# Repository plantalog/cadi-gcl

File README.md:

cadi-gcl
========
Meet these two:
Cadi GCL project is an open-source plant growth controller.
Grolly - is complete plant watering and feeding solution.

Grolly system is just based on Cadi hardware

Goal: to have an irrigation system that mixes up plant feeding solutions and provides it to the root system of the plants automatically. Has communication capabilities and two main working modes - automatic and manual. Has interface for remote advanced tuning of device's behavior.

FOLDER STRUCTURE
 
android:
    - Cadi Bluetooth Monitor for Android
    
cadiweb:
	contains Cadiweb server software for Cadi Remote Control.

hardware:
    - Eagle schematics (принципиальные схемы)
    - Topor PCB layouts (дизайны плат)
    - ulp file to convert Eagle schematics to Topor (скрипт конвертиования из Eagle в Topor)
    - schematics image files (растровые изображения дизайнов плат и схем)
    - STM32 bin flashing manual (как шить STM32 контроллеры bin файлами)
    
history:
    - old versions
    
manuals:
    - Cadi manuals
    - Cadi firmware code descriptions and architecture
    
raspberry:
    - Raspberry Pi software
    
stm32f100:
    - firmwares for STM32VL-Discovery boards
    
stm32f407:
    - firmwares for STM32F4-Discovery boards
    
win32:
    - Windows Qt Bluetooth data receiver software

check http://plantalog.livejournal.com for more info

Special thanks to creators of the tools and materials I used:
Schematics made with Eagle (http://www.cadsoftusa.com/)
PCB layouts in Topor (http://eda.eremex.ru/products/topor/)
STM32 firmwares are written using CooCox IDE (coocox.org)
Putty terminal (http://www.chiark.greenend.org.uk/~sgtatham/putty/)
STM32 ANs and PMs, STM.com ST-Link utility and libraries (st.com)

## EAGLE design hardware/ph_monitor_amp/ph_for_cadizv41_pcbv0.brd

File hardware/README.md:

flashing_stm32_with_bin_file explains how to flash STM32 uC with .bin file of firmware, using STM32 ST-Link utility

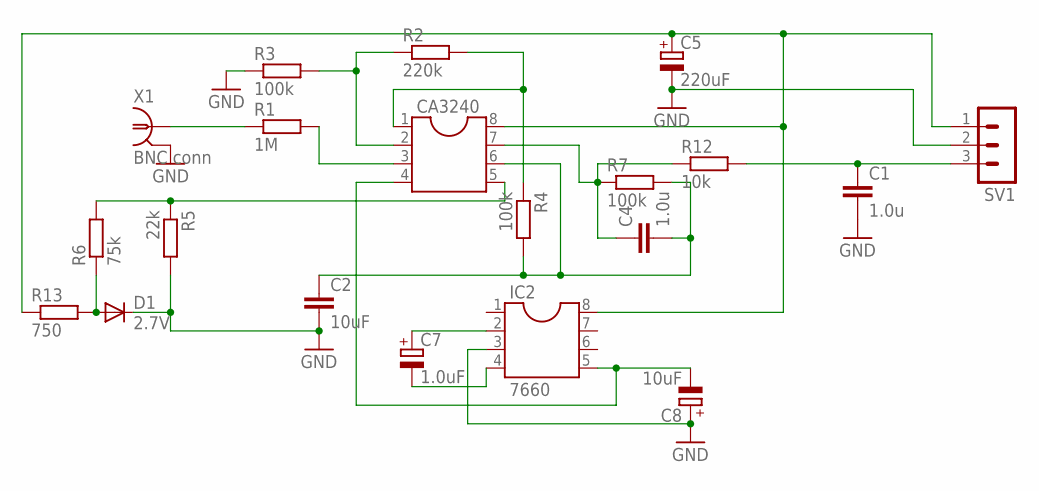
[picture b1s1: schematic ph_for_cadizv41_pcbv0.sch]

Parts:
C1, C4: 1.0u; C102-043X133
C2: 10uF; C102-043X133
C5: 220uF; E5-6
C7: 1.0uF; E5-6
C8: 10uF; E5-6
CA3240: DIL8; DIL08
D1: 2.7V; DO35-7
IC2: 7660; DIL08
R1: 1M; 0207/12
R2: 220k; 0207/12
R3, R4, R7: 100k; 0207/12
R5: 22k; 0207/12
R6: 75k; 0207/12
R12: 10k; 0207/12
R13: 750; 0207/12
SV1: MA03-1
X1: BNC conn; R141426

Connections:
GND: C1.2, C2.2, C5.-, C8.+, D1.C, IC2.3, R3.1, R5.2, SV1.2, X1.2 (GND), X1.3 (GND), X1.4 (GND), X1.5 (GND)
unnamed: CA3240.1, R2.2, R4.1
unnamed: CA3240.2, R2.1, R3.2
unnamed: CA3240.3, R1.2
unnamed: C7.+, IC2.2
unnamed: CA3240.5, R5.1, R6.2
unnamed: C7.-, IC2.4
unnamed: D1.A, R6.1, R13.2
unnamed: C4.1, CA3240.7, R7.1, R12.1
unnamed: C2.1, C4.2, CA3240.6, R4.2, R7.2
unnamed: C1.1, R12.2, SV1.3
unnamed: C8.-, CA3240.4, IC2.5
unnamed: R1.1, X1.1
unnamed: C5.+, CA3240.8, IC2.8, R13.1, SV1.1

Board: 2 copper layers, 20 parts (0 on the bottom side), 14 nets, no tracks yet.

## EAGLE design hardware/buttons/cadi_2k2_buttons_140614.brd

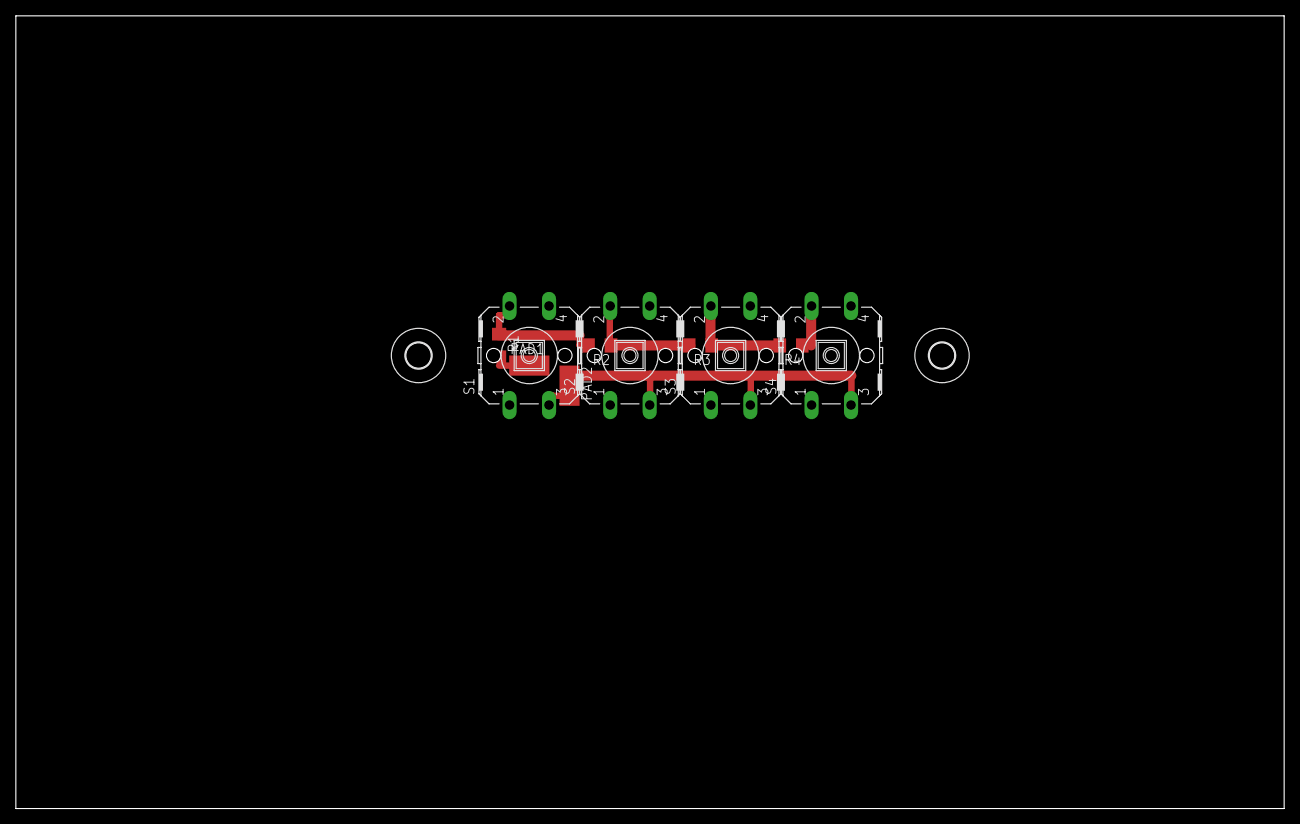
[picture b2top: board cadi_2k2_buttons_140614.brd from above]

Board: 2 copper layers, 160.0 x 100.0 mm, 12 parts (0 on the bottom side), 6 nets.

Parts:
H1, H2: MOUNT-HOLE3.2; 3,2
PAD1: VCC; SMD2,54-5,08
PAD2: TO_ADC; SMD2,54-5,08
R1, R2, R3, R4: 2k2; R1206
S1, S2, S3, S4: B3F-40XX

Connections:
unnamed: R4.1, S4.2
unnamed: R3.1, R4.2, S3.2
unnamed: R2.1, R3.2, S2.2
unnamed: R1.1, R2.2, S1.2
unnamed: PAD1.1, R1.2
unnamed: PAD2.1, S1.3, S2.3, S3.3, S4.3

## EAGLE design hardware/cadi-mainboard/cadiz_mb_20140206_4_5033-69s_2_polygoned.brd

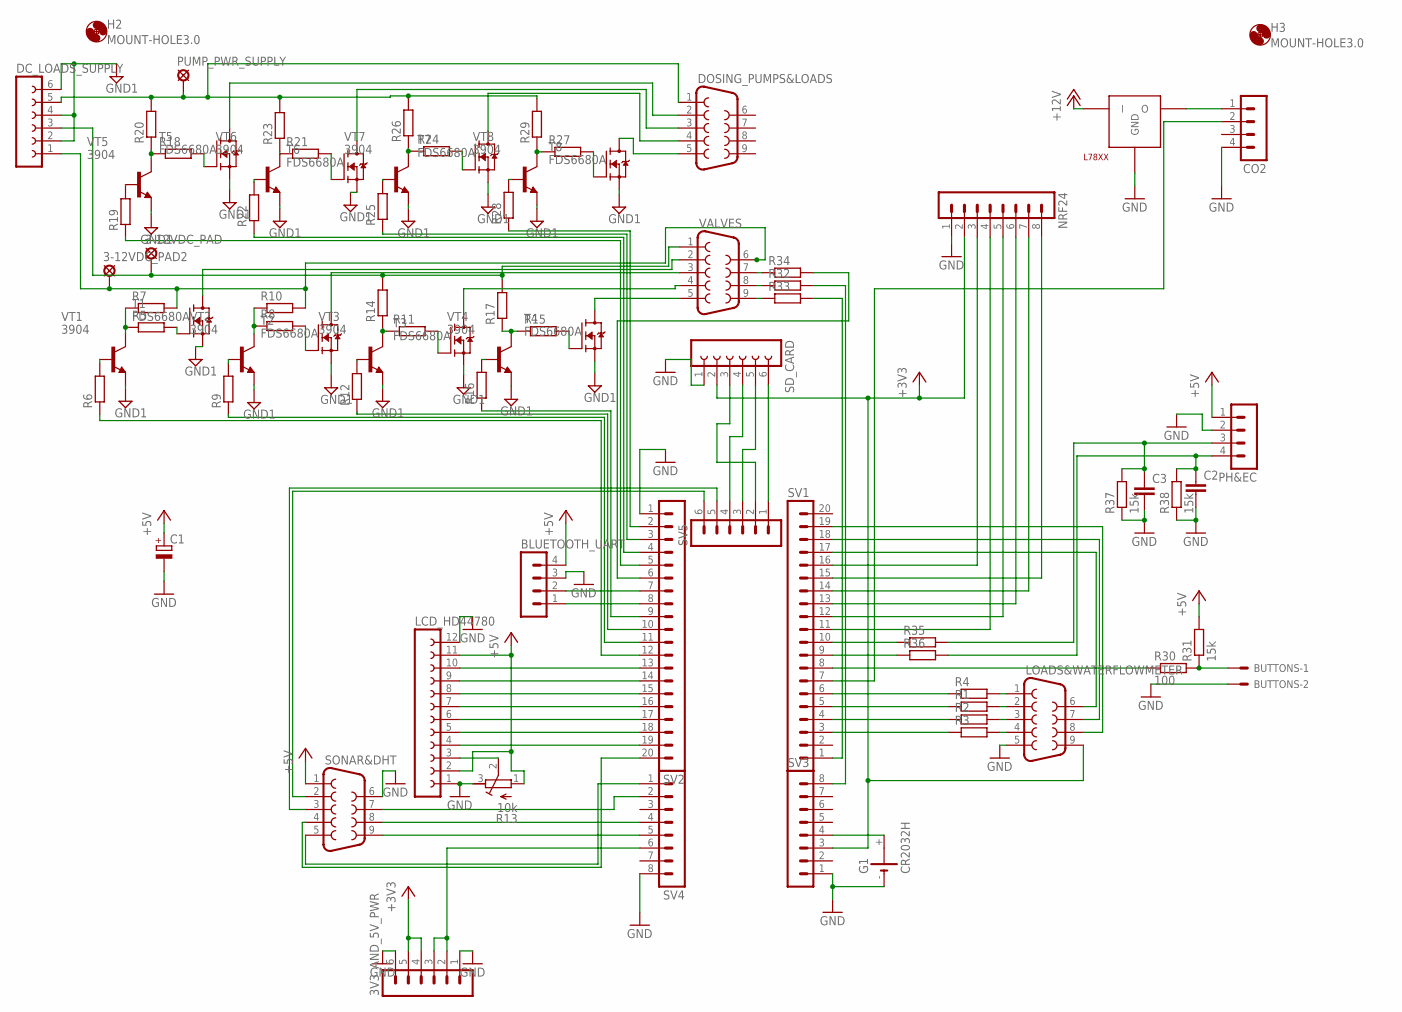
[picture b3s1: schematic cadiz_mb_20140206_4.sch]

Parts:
3-12VDC_PAD, 3-12VDC_PAD2: LSP13
3V3_AND_5V_PWR: MA06-1
BLUETOOTH_UART: MA04-1
BUTTONS: 22-23-2021
C1: CPOL-EUE5-13; E5-13
C2, C3: C-EUC1206; C1206
CO2: MA04-1
DC_LOADS_SUPPLY: FE06-1; FE06
DOSING_PUMPS&LOADS: F09HP
G1: CR2032H
H2, H3: MOUNT-HOLE3.0; 3,0
L7806: L78XX; TO220
LCD_HD44780: FE12-1; FE12
LOADS&WATERFLOWMETER: F09HP
NRF24: MA08-1
PH&EC: MA04-1
PUMP_PWR_SUPPLY: LSP13
R1, R2, R3, R4, R5, R6, R7, R8, R9, R10, R11, R12, R14, R15, R16, R17, R18, R19, R20, R21, R22, R23, R24, R25, R26, R27, R28, R29, R32, R33, R34, R35, R36: R-EU_M1206; M1206
R13: 10k; RTRIM3374
R30: 100; M1206
R31, R37, R38: 15k; M1206
SD_CARD: FE06-1; FE06
SONAR&DHT: F09HP
SV1, SV2: MA20-1
SV3, SV4: MA08-1
SV5: MA06-1
T1, T2, T3, T4, T5, T6, T7, T8: FDS6680A; SO8
VALVES: F09HP
VT1, VT2, VT3, VT4, VT5, VT6, VT7, VT8: 3904; SOT23

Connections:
+3V3: 3V3_AND_5V_PWR.4, 3V3_AND_5V_PWR.5, LOADS&WATERFLOWMETER.9, NRF24.2, SD_CARD.2, SV3.3
+5V: BLUETOOTH_UART.4, C1.+, LCD_HD44780.2, LCD_HD44780.11, PH&EC.1, R13.1 (E), R31.2, SONAR&DHT.1
+12V: L7806.IN (I)
GND: 3V3_AND_5V_PWR.1, 3V3_AND_5V_PWR.6, BLUETOOTH_UART.3, BUTTONS.2, C1.-, C2.2, C3.2, CO2.4, G1.-, L7806.GND, LCD_HD44780.1, LCD_HD44780.12, LOADS&WATERFLOWMETER.5, NRF24.1, PH&EC.2, R13.3 (A), R37.1, R38.1, SD_CARD.1, SONAR&DHT.6, SV2.1, SV3.1, SV4.8
GND1: DC_LOADS_SUPPLY.2, DC_LOADS_SUPPLY.4, DC_LOADS_SUPPLY.6, T1.SOURCE (S), T2.SOURCE (S), T3.SOURCE (S), T4.SOURCE (S), T5.SOURCE (S), T6.SOURCE (S), T7.SOURCE (S), T8.SOURCE (S), VT1.2 (E), VT2.2 (E), VT3.2 (E), VT4.2 (E), VT5.2 (E), VT6.2 (E), VT7.2 (E), VT8.2 (E)
unnamed: NRF24.6, SV1.13
unnamed: LCD_HD44780.4, SV2.19
unnamed: R16.1, SV2.9
unnamed: SONAR&DHT.2, SV5.6
unnamed: LCD_HD44780.3, R13.2 (S)
unnamed: G1.+, SV3.4
unnamed: LCD_HD44780.5, SV2.18
unnamed: LCD_HD44780.6, SV2.17
unnamed: LCD_HD44780.7, SV2.16
unnamed: LOADS&WATERFLOWMETER.3, R2.2
unnamed: LCD_HD44780.8, SV2.15
unnamed: R12.1, SV2.10
unnamed: LOADS&WATERFLOWMETER.4, R3.2
unnamed: LOADS&WATERFLOWMETER.2, R1.2
unnamed: LCD_HD44780.9, SV2.14
unnamed: LCD_HD44780.10, SV2.13
unnamed: SONAR&DHT.3, SV5.5
unnamed: R11.1, R14.1, VT3.3 (C)
unnamed: SD_CARD.6, SV5.1
unnamed: SONAR&DHT.7, SV4.2
unnamed: SD_CARD.5, SV5.3
unnamed: SD_CARD.4, SV5.4
unnamed: SONAR&DHT.8, SV4.4
unnamed: SD_CARD.3, SV5.2
unnamed: R1.1, SV1.5
unnamed: R2.1, SV1.4
unnamed: R3.1, SV1.3
unnamed: R4.1, SV1.6
unnamed: SONAR&DHT.9, SV4.5
unnamed: LOADS&WATERFLOWMETER.1, R4.2
unnamed: R8.2, T2.GATE (G)
unnamed: R5.2, T1.GATE (G)
unnamed: R6.2, VT1.1 (B)
unnamed: R9.2, VT2.1 (B)
unnamed: 3V3_AND_5V_PWR.2, 3V3_AND_5V_PWR.3, SV4.6
unnamed: R11.2, T3.GATE (G)
unnamed: R12.2, VT3.1 (B)
unnamed: R15.2, T4.GATE (G)
unnamed: R16.2, VT4.1 (B)
unnamed: R18.2, T5.GATE (G)
unnamed: R19.2, VT5.1 (B)
unnamed: R21.2, T6.GATE (G)
unnamed: R22.2, VT6.1 (B)
unnamed: R24.2, T7.GATE (G)
unnamed: R25.2, VT7.1 (B)
unnamed: R27.2, T8.GATE (G)
unnamed: R28.2, VT8.1 (B)
unnamed: 3-12VDC_PAD.MP, DC_LOADS_SUPPLY.3, R14.2, R17.2, VALVES.1
unnamed: 3-12VDC_PAD2.MP, DC_LOADS_SUPPLY.1, R7.2, R10.2, VALVES.6
unnamed: R9.1, SV2.11
unnamed: R6.1, SV2.12
unnamed: DC_LOADS_SUPPLY.5, DOSING_PUMPS&LOADS.1, PUMP_PWR_SUPPLY.MP, R20.2, R23.2, R26.2, R29.2
unnamed: BLUETOOTH_UART.1, SV2.8
unnamed: BLUETOOTH_UART.2, SV2.7
unnamed: R28.1, SV2.2
unnamed: R25.1, SV2.3
unnamed: R22.1, SV2.4
unnamed: R19.1, SV2.5
unnamed: DOSING_PUMPS&LOADS.5, T8.DRAIN (D)
unnamed: DOSING_PUMPS&LOADS.4, T7.DRAIN (D)
unnamed: DOSING_PUMPS&LOADS.3, T6.DRAIN (D)
unnamed: DOSING_PUMPS&LOADS.2, T5.DRAIN (D)
unnamed: BUTTONS.1, R30.2, R31.1
unnamed: NRF24.7, SV1.14
unnamed: NRF24.5, SV1.12
unnamed: R30.1, SV1.8
unnamed: T4.DRAIN (D), VALVES.5
unnamed: T3.DRAIN (D), VALVES.4
unnamed: T2.DRAIN (D), VALVES.3
unnamed: T1.DRAIN (D), VALVES.2
unnamed: R32.1, VALVES.8
unnamed: R33.1, VALVES.9
unnamed: R34.1, VALVES.7
unnamed: LOADS&WATERFLOWMETER.7, SV1.18
unnamed: LOADS&WATERFLOWMETER.8, SV1.19
unnamed: LOADS&WATERFLOWMETER.6, SV1.17
unnamed: SONAR&DHT.5, SV4.1
unnamed: SONAR&DHT.4, SV2.20
unnamed: NRF24.4, SV1.11
unnamed: NRF24.8, SV1.15
unnamed: NRF24.3, SV1.16
unnamed: R33.2, SV1.1
unnamed: R32.2, SV3.8
unnamed: R34.2, SV2.6
unnamed: C2.1, PH&EC.4, R36.2, R38.2
unnamed: C3.1, PH&EC.3, R35.2, R37.2
unnamed: R35.1, SV1.10
unnamed: R36.1, SV1.9
unnamed: CO2.1, L7806.OUT (O)
unnamed: CO2.2, SV1.7
VT1: R5.1, R7.1, VT1.3 (C)
VT2: R8.1, R10.1, VT2.3 (C)
VT4: R15.1, R17.1, VT4.3 (C)
VT5: R18.1, R20.1, VT5.3 (C)
VT6: R21.1, R23.1, VT6.3 (C)
VT7: R24.1, R26.1, VT7.3 (C)
VT8: R27.1, R29.1, VT8.3 (C)

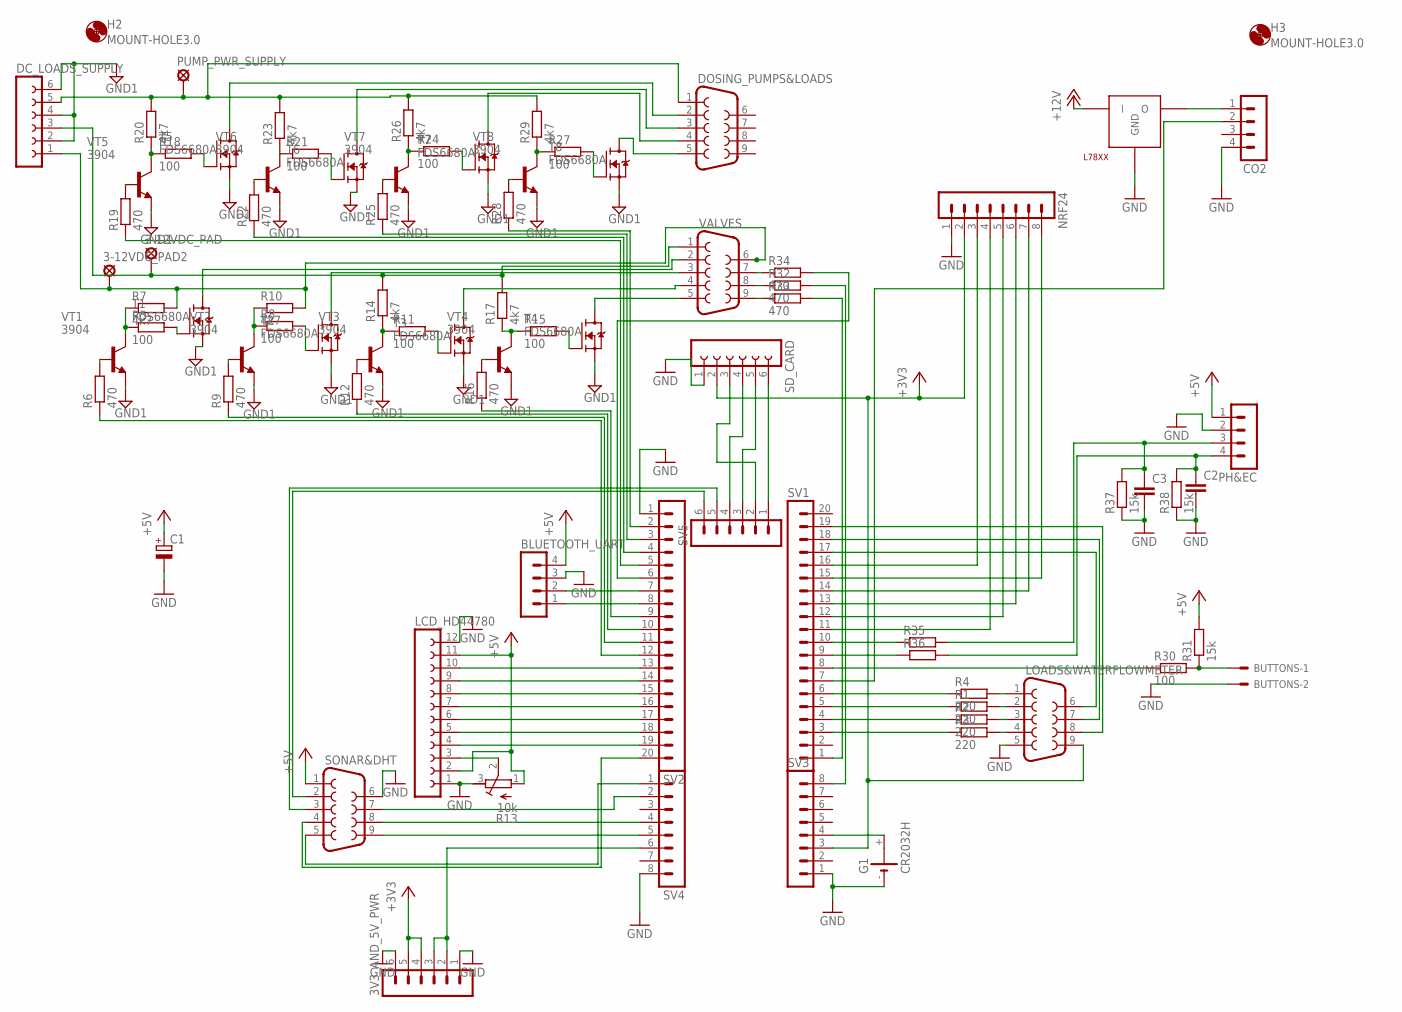
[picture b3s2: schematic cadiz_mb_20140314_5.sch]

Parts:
3-12VDC_PAD, 3-12VDC_PAD2: LSP13
3V3_AND_5V_PWR: MA06-1
BLUETOOTH_UART: MA04-1
BUTTONS: 22-23-2021
C1: CPOL-EUE5-13; E5-13
C2, C3: C-EUC1206; C1206
CO2: MA04-1
DC_LOADS_SUPPLY: FE06-1; FE06
DOSING_PUMPS&LOADS: F09HP
G1: CR2032H
H2, H3: MOUNT-HOLE3.0; 3,0
L7806: L78XX; TO220
LCD_HD44780: FE12-1; FE12
LOADS&WATERFLOWMETER: F09HP
NRF24: MA08-1
PH&EC: MA04-1
PUMP_PWR_SUPPLY: LSP13
R1, R2, R3, R4: 220; M1206
R5, R8, R11, R15, R18, R21, R24, R27, R30: 100; M1206
R6, R9, R12, R16, R19, R22, R25, R28, R32, R33, R34: 470; M1206
R7, R10, R14, R17, R20, R23, R26, R29: 4k7; M1206
R13: 10k; RTRIM3374
R31, R37, R38: 15k; M1206
R35, R36: R-EU_M1206; M1206
SD_CARD: FE06-1; FE06
SONAR&DHT: F09HP
SV1, SV2: MA20-1
SV3, SV4: MA08-1
SV5: MA06-1
T1, T2, T3, T4, T5, T6, T7, T8: FDS6680A; SO8
VALVES: F09HP
VT1, VT2, VT3, VT4, VT5, VT6, VT7, VT8: 3904; SOT23

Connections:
+3V3: 3V3_AND_5V_PWR.4, 3V3_AND_5V_PWR.5, LOADS&WATERFLOWMETER.9, NRF24.2, SD_CARD.2, SV3.3
+5V: BLUETOOTH_UART.4, C1.+, LCD_HD44780.2, LCD_HD44780.11, PH&EC.1, R13.1 (E), R31.2, SONAR&DHT.1
+12V: L7806.IN (I)
GND: 3V3_AND_5V_PWR.1, 3V3_AND_5V_PWR.6, BLUETOOTH_UART.3, BUTTONS.2, C1.-, C2.2, C3.2, CO2.4, G1.-, L7806.GND, LCD_HD44780.1, LCD_HD44780.12, LOADS&WATERFLOWMETER.5, NRF24.1, PH&EC.2, R13.3 (A), R37.1, R38.1, SD_CARD.1, SONAR&DHT.6, SV2.1, SV3.1, SV4.8
GND1: DC_LOADS_SUPPLY.2, DC_LOADS_SUPPLY.4, DC_LOADS_SUPPLY.6, T1.SOURCE (S), T2.SOURCE (S), T3.SOURCE (S), T4.SOURCE (S), T5.SOURCE (S), T6.SOURCE (S), T7.SOURCE (S), T8.SOURCE (S), VT1.2 (E), VT2.2 (E), VT3.2 (E), VT4.2 (E), VT5.2 (E), VT6.2 (E), VT7.2 (E), VT8.2 (E)
unnamed: NRF24.6, SV1.13
unnamed: LCD_HD44780.4, SV2.19
unnamed: R16.1, SV2.9
unnamed: SONAR&DHT.2, SV5.6
unnamed: LCD_HD44780.3, R13.2 (S)
unnamed: G1.+, SV3.4
unnamed: LCD_HD44780.5, SV2.18
unnamed: LCD_HD44780.6, SV2.17
unnamed: LCD_HD44780.7, SV2.16
unnamed: LOADS&WATERFLOWMETER.3, R2.2
unnamed: LCD_HD44780.8, SV2.15
unnamed: R12.1, SV2.10
unnamed: LOADS&WATERFLOWMETER.4, R3.2
unnamed: LOADS&WATERFLOWMETER.2, R1.2
unnamed: LCD_HD44780.9, SV2.14
unnamed: LCD_HD44780.10, SV2.13
unnamed: SONAR&DHT.3, SV5.5
unnamed: R11.1, R14.1, VT3.3 (C)
unnamed: SD_CARD.6, SV5.1
unnamed: SONAR&DHT.7, SV4.2
unnamed: SD_CARD.5, SV5.3
unnamed: SD_CARD.4, SV5.4
unnamed: SONAR&DHT.8, SV4.4
unnamed: SD_CARD.3, SV5.2
unnamed: R1.1, SV1.5
unnamed: R2.1, SV1.4
unnamed: R3.1, SV1.3
unnamed: R4.1, SV1.6
unnamed: SONAR&DHT.9, SV4.5
unnamed: LOADS&WATERFLOWMETER.1, R4.2
unnamed: R8.2, T2.GATE (G)
unnamed: R5.2, T1.GATE (G)
unnamed: R6.2, VT1.1 (B)
unnamed: R9.2, VT2.1 (B)
unnamed: 3V3_AND_5V_PWR.2, 3V3_AND_5V_PWR.3, SV4.6
unnamed: R11.2, T3.GATE (G)
unnamed: R12.2, VT3.1 (B)
unnamed: R15.2, T4.GATE (G)
unnamed: R16.2, VT4.1 (B)
unnamed: R18.2, T5.GATE (G)
unnamed: R19.2, VT5.1 (B)
unnamed: R21.2, T6.GATE (G)
unnamed: R22.2, VT6.1 (B)
unnamed: R24.2, T7.GATE (G)
unnamed: R25.2, VT7.1 (B)
unnamed: R27.2, T8.GATE (G)
unnamed: R28.2, VT8.1 (B)
unnamed: 3-12VDC_PAD.MP, DC_LOADS_SUPPLY.3, R14.2, R17.2, VALVES.1
unnamed: 3-12VDC_PAD2.MP, DC_LOADS_SUPPLY.1, R7.2, R10.2, VALVES.6
unnamed: R9.1, SV2.11
unnamed: R6.1, SV2.12
unnamed: DC_LOADS_SUPPLY.5, DOSING_PUMPS&LOADS.1, PUMP_PWR_SUPPLY.MP, R20.2, R23.2, R26.2, R29.2
unnamed: BLUETOOTH_UART.1, SV2.8
unnamed: BLUETOOTH_UART.2, SV2.7
unnamed: R28.1, SV2.2
unnamed: R25.1, SV2.3
unnamed: R22.1, SV2.4
unnamed: R19.1, SV2.5
unnamed: DOSING_PUMPS&LOADS.5, T8.DRAIN (D)
unnamed: DOSING_PUMPS&LOADS.4, T7.DRAIN (D)
unnamed: DOSING_PUMPS&LOADS.3, T6.DRAIN (D)
unnamed: DOSING_PUMPS&LOADS.2, T5.DRAIN (D)
unnamed: BUTTONS.1, R30.2, R31.1
unnamed: NRF24.7, SV1.14
unnamed: NRF24.5, SV1.12
unnamed: R30.1, SV1.8
unnamed: T4.DRAIN (D), VALVES.5
unnamed: T3.DRAIN (D), VALVES.4
unnamed: T2.DRAIN (D), VALVES.3
unnamed: T1.DRAIN (D), VALVES.2
unnamed: R32.1, VALVES.8
unnamed: R33.1, VALVES.9
unnamed: R34.1, VALVES.7
unnamed: LOADS&WATERFLOWMETER.7, SV1.18
unnamed: LOADS&WATERFLOWMETER.8, SV1.19
unnamed: LOADS&WATERFLOWMETER.6, SV1.17
unnamed: SONAR&DHT.5, SV4.1
unnamed: SONAR&DHT.4, SV2.20
unnamed: NRF24.4, SV1.11
unnamed: NRF24.8, SV1.15
unnamed: NRF24.3, SV1.16
unnamed: R33.2, SV1.1
unnamed: R32.2, SV3.8
unnamed: R34.2, SV2.6
unnamed: C2.1, PH&EC.4, R36.2, R38.2
unnamed: C3.1, PH&EC.3, R35.2, R37.2
unnamed: R35.1, SV1.10
unnamed: R36.1, SV1.9
unnamed: CO2.1, L7806.OUT (O)
unnamed: CO2.2, SV1.7
VT1: R5.1, R7.1, VT1.3 (C)
VT2: R8.1, R10.1, VT2.3 (C)
VT4: R15.1, R17.1, VT4.3 (C)
VT5: R18.1, R20.1, VT5.3 (C)
VT6: R21.1, R23.1, VT6.3 (C)
VT7: R24.1, R26.1, VT7.3 (C)
VT8: R27.1, R29.1, VT8.3 (C)

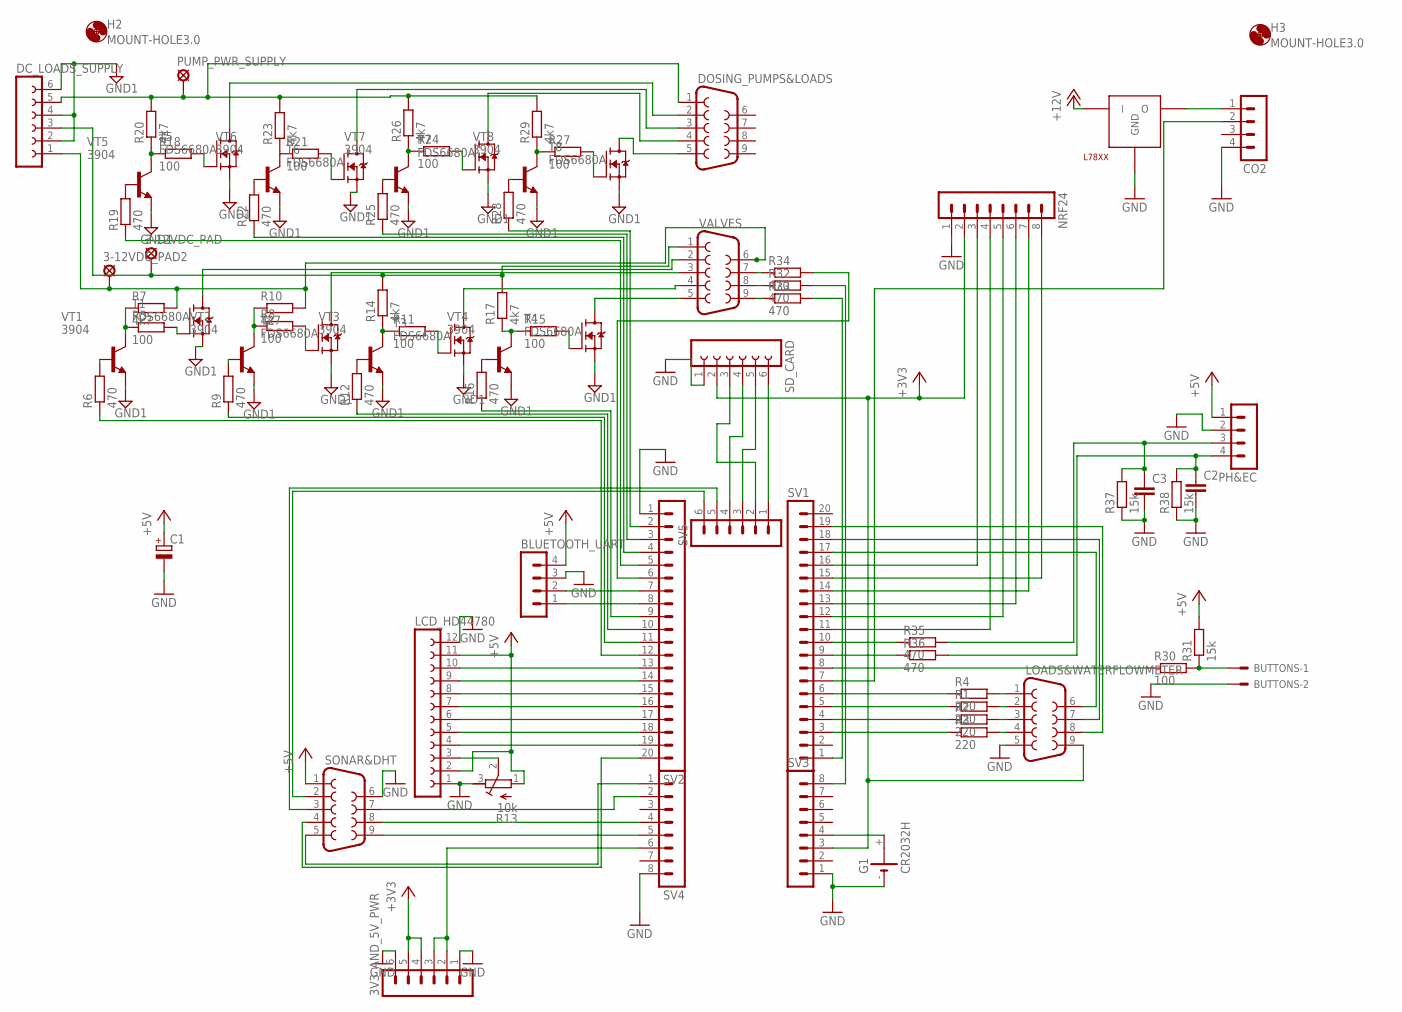
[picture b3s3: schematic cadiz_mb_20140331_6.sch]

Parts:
3-12VDC_PAD, 3-12VDC_PAD2: LSP13
3V3_AND_5V_PWR: MA06-1
BLUETOOTH_UART: MA04-1
BUTTONS: 22-23-2021
C1: CPOL-EUE5-13; E5-13
C2, C3: C-EUC1206; C1206
CO2: MA04-1
DC_LOADS_SUPPLY: FE06-1; FE06
DOSING_PUMPS&LOADS: F09HP
G1: CR2032H
H2, H3: MOUNT-HOLE3.0; 3,0
L7806: L78XX; TO220
LCD_HD44780: FE12-1; FE12
LOADS&WATERFLOWMETER: F09HP
NRF24: MA08-1
PH&EC: MA04-1
PUMP_PWR_SUPPLY: LSP13
R1, R2, R3, R4: 220; M1206
R5, R8, R11, R15, R18, R21, R24, R27, R30: 100; M1206
R6, R9, R12, R16, R19, R22, R25, R28, R32, R33, R34, R35, R36: 470; M1206
R7, R10, R14, R17, R20, R23, R26, R29: 4k7; M1206
R13: 10k; RTRIM3374
R31, R37, R38: 15k; M1206
SD_CARD: FE06-1; FE06
SONAR&DHT: F09HP
SV1, SV2: MA20-1
SV3, SV4: MA08-1
SV5: MA06-1
T1, T2, T3, T4, T5, T6, T7, T8: FDS6680A; SO8
VALVES: F09HP
VT1, VT2, VT3, VT4, VT5, VT6, VT7, VT8: 3904; SOT23

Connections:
+3V3: 3V3_AND_5V_PWR.4, 3V3_AND_5V_PWR.5, LOADS&WATERFLOWMETER.9, NRF24.2, SD_CARD.2, SV3.3
+5V: BLUETOOTH_UART.4, C1.+, LCD_HD44780.2, LCD_HD44780.11, PH&EC.1, R13.1 (E), R31.2, SONAR&DHT.1
+12V: L7806.IN (I)
GND: 3V3_AND_5V_PWR.1, 3V3_AND_5V_PWR.6, BLUETOOTH_UART.3, BUTTONS.2, C1.-, C2.2, C3.2, CO2.4, G1.-, L7806.GND, LCD_HD44780.1, LCD_HD44780.12, LOADS&WATERFLOWMETER.5, NRF24.1, PH&EC.2, R13.3 (A), R37.1, R38.1, SD_CARD.1, SONAR&DHT.6, SV2.1, SV3.1, SV4.8
GND1: DC_LOADS_SUPPLY.2, DC_LOADS_SUPPLY.4, DC_LOADS_SUPPLY.6, T1.SOURCE (S), T2.SOURCE (S), T3.SOURCE (S), T4.SOURCE (S), T5.SOURCE (S), T6.SOURCE (S), T7.SOURCE (S), T8.SOURCE (S), VT1.2 (E), VT2.2 (E), VT3.2 (E), VT4.2 (E), VT5.2 (E), VT6.2 (E), VT7.2 (E), VT8.2 (E)
unnamed: NRF24.6, SV1.13
unnamed: LCD_HD44780.4, SV2.19
unnamed: R16.1, SV2.9
unnamed: SONAR&DHT.2, SV5.6
unnamed: LCD_HD44780.3, R13.2 (S)
unnamed: G1.+, SV3.4
unnamed: LCD_HD44780.5, SV2.18
unnamed: LCD_HD44780.6, SV2.17
unnamed: LCD_HD44780.7, SV2.16
unnamed: LOADS&WATERFLOWMETER.3, R2.2
unnamed: LCD_HD44780.8, SV2.15
unnamed: R12.1, SV2.10
unnamed: LOADS&WATERFLOWMETER.4, R3.2
unnamed: LOADS&WATERFLOWMETER.2, R1.2
unnamed: LCD_HD44780.9, SV2.14
unnamed: LCD_HD44780.10, SV2.13
unnamed: SONAR&DHT.3, SV5.5
unnamed: R11.1, R14.1, VT3.3 (C)
unnamed: SD_CARD.6, SV5.1
unnamed: SONAR&DHT.7, SV4.2
unnamed: SD_CARD.5, SV5.3
unnamed: SD_CARD.4, SV5.4
unnamed: SONAR&DHT.8, SV4.4
unnamed: SD_CARD.3, SV5.2
unnamed: R1.1, SV1.5
unnamed: R2.1, SV1.4
unnamed: R3.1, SV1.3
unnamed: R4.1, SV1.6
unnamed: SONAR&DHT.9, SV4.5
unnamed: LOADS&WATERFLOWMETER.1, R4.2
unnamed: R8.2, T2.GATE (G)
unnamed: R5.2, T1.GATE (G)
unnamed: R6.2, VT1.1 (B)
unnamed: R9.2, VT2.1 (B)
unnamed: 3V3_AND_5V_PWR.2, 3V3_AND_5V_PWR.3, SV4.6
unnamed: R11.2, T3.GATE (G)
unnamed: R12.2, VT3.1 (B)
unnamed: R15.2, T4.GATE (G)
unnamed: R16.2, VT4.1 (B)
unnamed: R18.2, T5.GATE (G)
unnamed: R19.2, VT5.1 (B)
unnamed: R21.2, T6.GATE (G)
unnamed: R22.2, VT6.1 (B)
unnamed: R24.2, T7.GATE (G)
unnamed: R25.2, VT7.1 (B)
unnamed: R27.2, T8.GATE (G)
unnamed: R28.2, VT8.1 (B)
unnamed: 3-12VDC_PAD.MP, DC_LOADS_SUPPLY.3, R14.2, R17.2, VALVES.1
unnamed: 3-12VDC_PAD2.MP, DC_LOADS_SUPPLY.1, R7.2, R10.2, VALVES.6
unnamed: R9.1, SV2.11
unnamed: R6.1, SV2.12
unnamed: DC_LOADS_SUPPLY.5, DOSING_PUMPS&LOADS.1, PUMP_PWR_SUPPLY.MP, R20.2, R23.2, R26.2, R29.2
unnamed: BLUETOOTH_UART.1, SV2.8
unnamed: BLUETOOTH_UART.2, SV2.7
unnamed: R28.1, SV2.2
unnamed: R25.1, SV2.3
unnamed: R22.1, SV2.4
unnamed: R19.1, SV2.5
unnamed: DOSING_PUMPS&LOADS.5, T8.DRAIN (D)
unnamed: DOSING_PUMPS&LOADS.4, T7.DRAIN (D)
unnamed: DOSING_PUMPS&LOADS.3, T6.DRAIN (D)
unnamed: DOSING_PUMPS&LOADS.2, T5.DRAIN (D)
unnamed: BUTTONS.1, R30.2, R31.1
unnamed: NRF24.7, SV1.14
unnamed: NRF24.5, SV1.12
unnamed: R30.1, SV1.8
unnamed: T4.DRAIN (D), VALVES.5
unnamed: T3.DRAIN (D), VALVES.4
unnamed: T2.DRAIN (D), VALVES.3
unnamed: T1.DRAIN (D), VALVES.2
unnamed: R32.1, VALVES.8
unnamed: R33.1, VALVES.9
unnamed: R34.1, VALVES.7
unnamed: LOADS&WATERFLOWMETER.7, SV1.18
unnamed: LOADS&WATERFLOWMETER.8, SV1.19
unnamed: LOADS&WATERFLOWMETER.6, SV1.17
unnamed: SONAR&DHT.5, SV4.1
unnamed: SONAR&DHT.4, SV2.20
unnamed: NRF24.4, SV1.11
unnamed: NRF24.8, SV1.15
unnamed: NRF24.3, SV1.16
unnamed: R33.2, SV1.1
unnamed: R32.2, SV3.8
unnamed: R34.2, SV2.6
unnamed: C2.1, PH&EC.4, R36.2, R38.2
unnamed: C3.1, PH&EC.3, R35.2, R37.2
unnamed: R35.1, SV1.10
unnamed: R36.1, SV1.9
unnamed: CO2.1, L7806.OUT (O)
unnamed: CO2.2, SV1.7
VT1: R5.1, R7.1, VT1.3 (C)
VT2: R8.1, R10.1, VT2.3 (C)
VT4: R15.1, R17.1, VT4.3 (C)
VT5: R18.1, R20.1, VT5.3 (C)
VT6: R21.1, R23.1, VT6.3 (C)
VT7: R24.1, R26.1, VT7.3 (C)
VT8: R27.1, R29.1, VT8.3 (C)

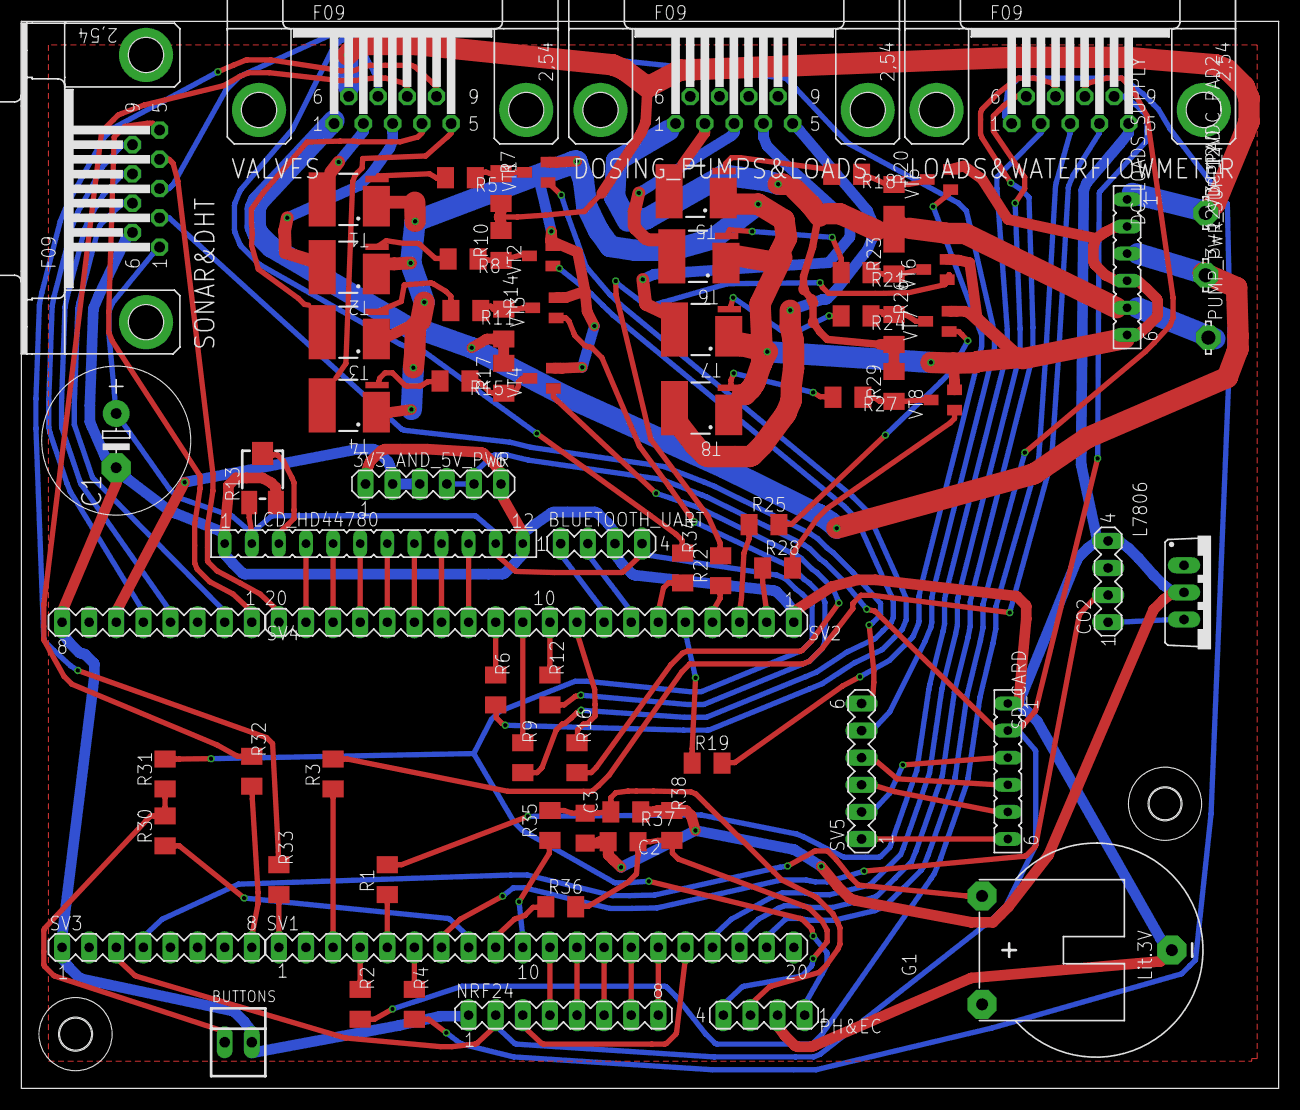
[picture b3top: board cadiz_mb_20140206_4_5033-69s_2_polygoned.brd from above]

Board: 2 copper layers, 117.8 x 100.0 mm, 82 parts (0 on the bottom side), 101 nets.

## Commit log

2013-12-14 gcl initial commit
2013-12-14 - timer system v2 specifications added
2013-12-14 firmware description
2013-12-15 F4 fw architecture
2013-12-16 Cadi & Cadi2 firmware architectures
2013-12-16 mm, danone
2013-12-17 wiring diagrams
2013-12-17 removed link to VERSION_BUILD for successful building
2013-12-17 information update & ticket creation
2013-12-23 USART transfer
2013-12-23 HowTO Cadi assembly
2013-12-29 v1.3
2013-12-30 30dec2013
2014-01-05 PWM MOSFET driver
2014-01-06 v1.4 cadi fw
2014-01-06 Cadi wiring diagram v1.4
2014-01-06 cadi fw v1.4 docs
2014-01-06 mycontroller.ru backuped articles (Russian)
2014-01-10 watering circuit
2014-01-23 cadi fw 1.5
2014-02-17 cadi function list
2014-02-26 protocol
2014-02-26 user manual
2014-02-28 basic comm test
2014-03-01 cadiweb bt connection
2014-03-01 cadiweb bt 2
2014-03-02 v 1.7 support
2014-03-02 cadi fw 1.7
2014-03-08 140308
2014-03-18 cadi mb fw
2014-03-24 adc and dht rework
2014-03-30 psi sens cal
2014-03-30 booster pump config
2014-03-31 printOk usability
2014-04-08 comm updates
2014-04-10 cadiweb comm
2014-04-10 cadiweb interface
2014-04-21 Cadi fw v2
2014-04-21 open/close valves
2014-04-21 clear failed flags
2014-04-24 sonar
2014-04-27 cadiweb and fw
2014-04-28 40byte status packets
2014-04-29 valves hotfix
2014-05-02 btd stream
2014-05-02 svg and proto
2014-05-04 finally!
2014-05-05 cadi fw 2.1
2014-05-05 changes in 2.1
2014-05-07 2.1.1
2014-05-08 mb2 fix
2014-05-09 cadi mb dimensions
2014-05-09 cadi mb (6) schematics
2014-05-09 cadiweb
2014-05-11 svg draw on client side
2014-05-11 v2.1.1 autoshutdown added
2014-05-12 status/flags
2014-05-12 dht and sonar splitter
2014-05-13 also video
2014-06-02 installer
2014-06-02 ubuntu1404deploy
2014-06-02 reboot
2014-06-03 ubuntu 12.04 installation script
2014-06-04 cadiweb install
2014-06-04 cadiweb deploy scripts
2014-06-06 current
2014-06-12 btns & svg
2014-06-13 dosing by time
2014-06-14 daily
2014-06-15 readmes
2014-06-16 cw update
2014-06-16 install
2014-08-27 grolly and cadi fw
2014-08-27 grolly src
2014-09-04 grolly alpha 7
2014-09-04 BTDaemon: rx_ee introduced
2014-09-04 Grolly tech manual
2014-09-04 rebranding
2014-09-06 grolly fw 1.1.a1
2014-09-06 cadi settings sync online
2014-09-07 grolly 1.1_a3
2014-09-07 watchdog in uart_task
2014-09-07 Simple WP for Grolly
2014-09-08 cadi reset regression fix
2014-09-08 eeprom_test regression fix
2014-09-08 v1.1b2 lstasks
2014-09-09 v1.1b3
2014-09-10 grolly fw 1.1 b4
2014-09-10 timer applied to WP
2014-10-04 cadiweb for raspberry
2014-10-04 grolly1.1b6
2014-10-05 binaries
2014-10-05 ArchLinux for Pi
2014-10-26 carbomat service man
2014-10-26 carbomat
2014-10-26 carbodocs
